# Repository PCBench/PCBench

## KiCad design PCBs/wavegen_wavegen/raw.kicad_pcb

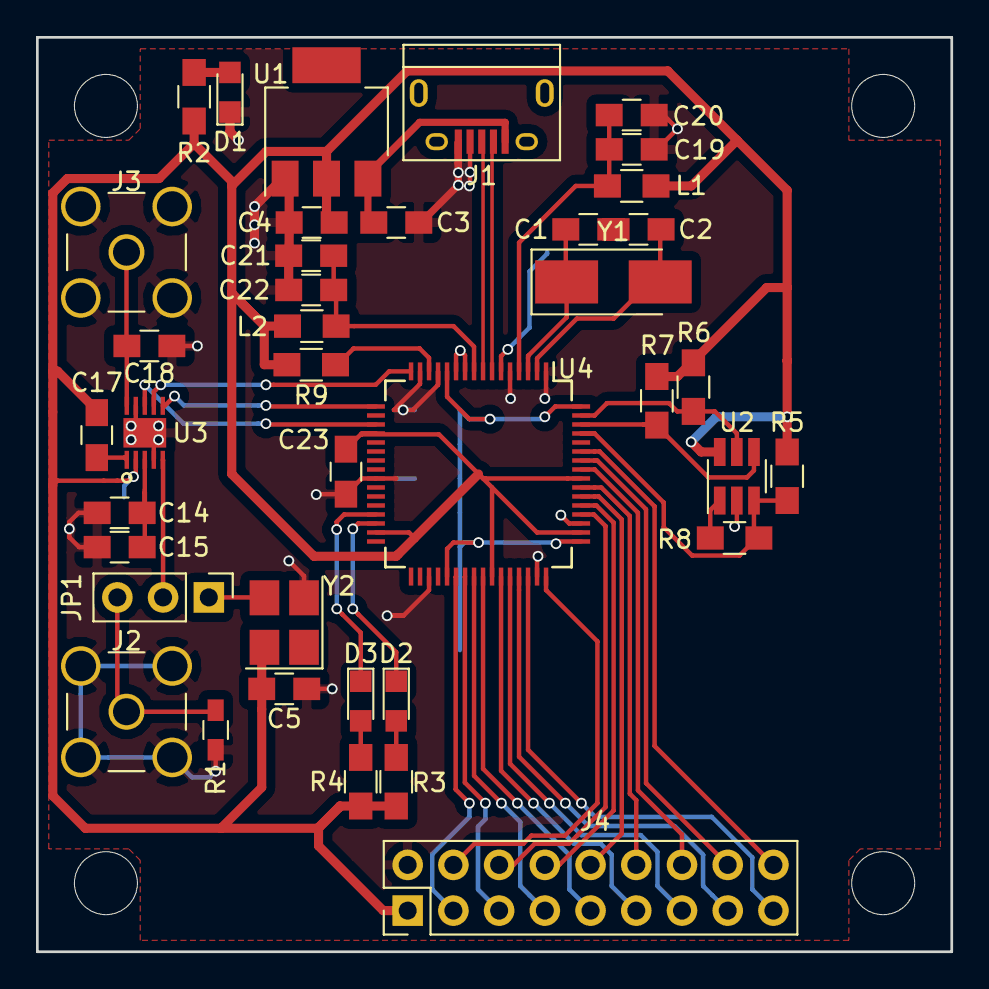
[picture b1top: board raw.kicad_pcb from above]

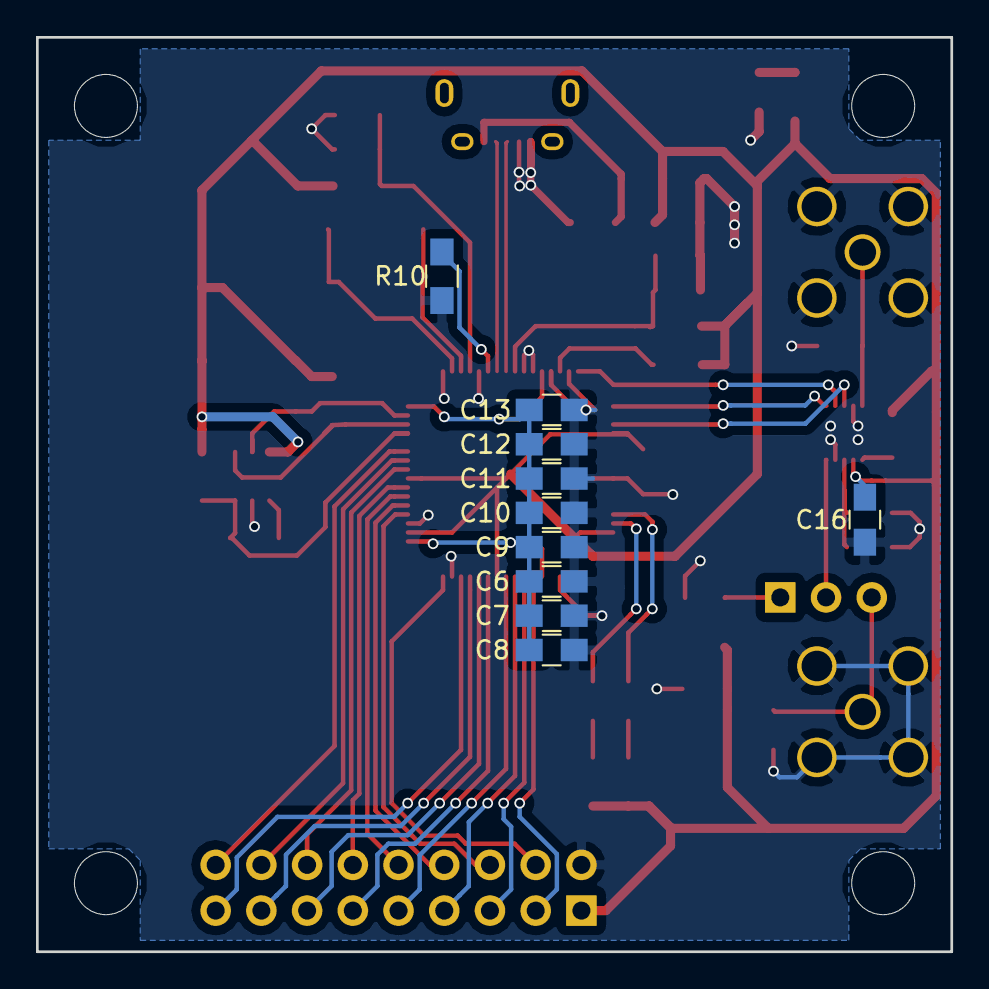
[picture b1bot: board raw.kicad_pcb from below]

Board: 2 copper layers, 50.8 x 50.8 mm, 49 parts (10 on the bottom side), 47 nets.

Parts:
C1, C2: 27p; C_0805_HandSoldering
C3, C5, C7, C8, C9, C10, C11, C12, C13, C14, C16, C18, C20, C22, C23: 100n; C_0805_HandSoldering
C4, C15: 10u; C_0805_HandSoldering
C6: 3.3u; C_0805_HandSoldering
C17: 10n; C_0805_HandSoldering
C19, C21: 4.7u; C_0805_HandSoldering
D1, D2, D3: LED_Small; LED_0805
J1: USB_B; USB_Micro-B
J2: EXT_CLK; SMA_THT_Jack_Straight
J3: VOUT; SMA_THT_Jack_Straight
J4: CONN_02X09; Pin_Header_Straight_2x09_Pitch2.54mm
JP1: CLK_SELECT; Pin_Header_Straight_1x03_Pitch2.54mm
L1, L2: 800m; L_0805_HandSoldering
R1: 50; R_0603_HandSoldering
R2, R3, R4: 470; R_0805_HandSoldering
R5, R6, R7: 10k; R_0805_HandSoldering
R8: 2.2k; R_0805_HandSoldering
R9: 1k; R_0805_HandSoldering
R10: 12k; R_0805_HandSoldering
U1: LD1117S33TR; SOT-223
U2: 93LC46BT; SOT-23-6_Handsoldering
U3: AD9837
U4: FT2232H; LQFP-64_10x10mm_Pitch0.5mm
Y1: 12MHz; Crystal_SMD_5032-2pin_5.0x3.2mm_HandSoldering
Y2: OXETGCJANF; Oscillator_SMD_Abracon_ASE-4pin_3.2x2.5mm_HandSoldering

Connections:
+3V3: C4.1, C5.1, C16.1, C17.1, C23.1, J4.1, L1.1, L2.1, R2.2, R3.2, R4.2, R5.1, R6.1, R7.1, R9.2, U1.2, U2.6, U3.2, U4.20, U4.31, U4.42, U4.50, U4.56, Y2.4
DAC_CLK: JP1.2, U3.5
EECLK: R7.2, U2.4, U4.62
EECS: R6.2, U2.5, U4.63
EEDATA: R5.2, R8.1, U2.3, U4.61
FTOSCI: C2.1, U4.2, Y1.2
FTOSCO: C1.1, U4.3, Y1.1
FTRXLED: D3.1, U4.29
FTTXLED: D2.1, U4.30
FTVPHY: C19.1, C20.1, L1.2, U4.4
FTVPLL: C21.1, C22.1, L2.2, U4.9
GNDA: C3.2, C4.2, C5.2, C6.2, C7.2, C8.2, C9.2, C10.2, C11.2, C12.2, C13.2, C14.2, C15.2, C16.2, C18.2, C19.2, C20.2, C21.2, C22.2, C23.2, D1.1, J1.4, J1.5, J2.2, J3.2, J4.2, R1.2, R10.2, U1.1, U2.2, U3.4, U3.9, U3.11, U4.1, U4.5, U4.10, U4.11, U4.13, U4.15, U4.25, U4.35, U4.47, U4.51, Y2.2
unnamed: C1.2, C2.2
unnamed: C3.1, J1.1, U1.3
unnamed: C6.1, C7.1, C8.1, C9.1, C10.1, C11.1, C12.1, C13.1, U4.12, U4.37, U4.49, U4.64
unnamed: C14.1, C15.1, U3.3
unnamed: C17.2, U3.1
unnamed: C18.1, J3.1, U3.10
unnamed: D1.2, R2.1
unnamed: D2.2, R3.1
unnamed: D3.2, R4.1
unnamed: J2.1, JP1.3, R1.1
unnamed: J4.3, U4.38
unnamed: J4.4, U4.48
unnamed: J4.5, U4.39
unnamed: J4.6, U4.52
unnamed: J4.7, U4.40
unnamed: J4.8, U4.53
unnamed: J4.9, U4.41
unnamed: J4.10, U4.54
unnamed: J4.11, U4.43
unnamed: J4.12, U4.55
unnamed: J4.13, U4.44
unnamed: J4.14, U4.57
unnamed: J4.15, U4.45
unnamed: J4.16, U4.58
unnamed: J4.17, U4.46
unnamed: J4.18, U4.59
unnamed: JP1.1, Y2.3
unnamed: R8.2, U2.1
unnamed: R9.1, U4.14
unnamed: R10.1, U4.6
unnamed: U3.6, U4.17
unnamed: U3.7, U4.16
unnamed: U3.8, U4.19
USB_D+: J1.3, U4.8
USB_D-: J1.2, U4.7

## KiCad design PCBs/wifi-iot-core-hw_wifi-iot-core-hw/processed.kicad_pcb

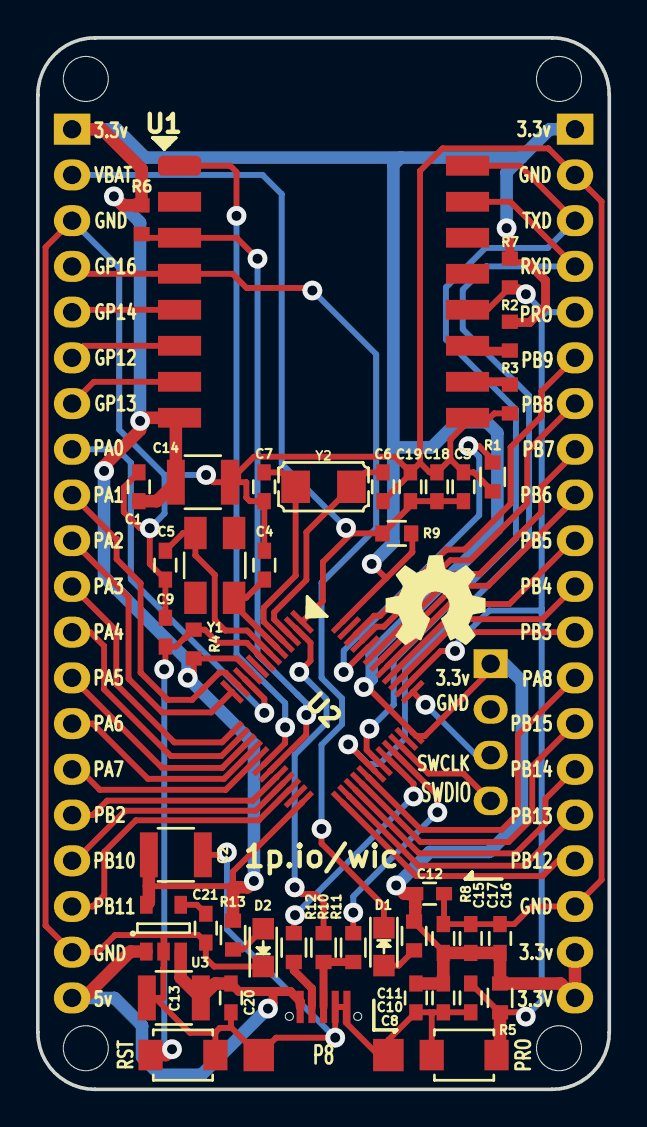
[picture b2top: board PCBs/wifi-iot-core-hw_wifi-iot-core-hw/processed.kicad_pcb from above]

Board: 2 copper layers, 31.8 x 58.4 mm, 52 parts (0 on the bottom side), 54 nets.

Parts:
C1, C9, C10, C11, C12, C15, C17, C19, C20: 0.1uF; C_0603
C2, C13, C14: 10uF-50v; C_1210
C3: 100nF; C_0603
C4, C5: 10pF; C_0603
C6: 15pF; C_0603
C7: 15pf; C_0603
C8: 470pF; C_0603
C16, C18: 1uF; C_0603
C21: 10nF; C_0603
D1: Led GPIO16; LED_0805
D2: Led; LED_0805
P1, P2: CONN_01X20; Pin_Header_Straight_1x20
P3, P4, P5, P6: CONN_01X01; MountingHole_2.5mm
P7: CONN_01X04; Pin_Header_Straight_1x04
P8: USB; Micro_usb_B_smd
PRO: SW_PUSH_SMALL_H; SW_SPST_B3U-1000P-B
R1, R6, R7, R8, R13: 10k; R_0603
R2, R3, R4, R5: 10K; R_0603
R9: 0R; R_0603
R10: 1.5K; R_0603
R11, R12: 22; R_0603
RST: RST; SW_SPST_B3U-1000P-B
U1: ESP-07v2; ESP-07v2-smd-16pin
U2: STM32F103C8Tx; LQFP-48_Pin1.7x0.3mm_Pitch0.5mm
U3: LP2985LV; SOT-23-5
VAL**: oshw_logo_500; logo5
Y1: 8MHz; Crystal_SMD_5032_4Pads
Y2: 32.687; crystal_smd_32.768_2Pin

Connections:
+3V3: C1.1, C2.1, C10.2, C11.2, C12.1, C14.1, C15.2, C16.2, C17.2, P1.1, P2.1, P2.19, P2.20, P7.1, R2.1, R4.2, R5.2, R6.1, R7.1, R8.1, R9.2, R13.1, U1.8, U2.9, U2.24, U2.36, U2.48, U3.5
+5V: C13.1, C20.1, P1.20, P8.1, U3.1, U3.3
/CH_PD: R6.2, U1.3, U2.19
/ESP_PRO: C8.1, P2.5, PRO.1, R5.1, R7.2, U1.12, U2.38
/ESP_RST: U1.1, U2.18
/ESP_RXD: P2.4, U1.15, U2.30
/ESP_TXD: P2.3, U1.16, U2.31
/GPIO16: D1.1, P1.4, U1.4
/RST: C9.1, R4.1, RST.1, U2.7
/SWCLK: P7.3, U2.37
/SWDIO: P7.4, U2.34
/USB_DIS: R10.1, U2.2
/USB_DM: R12.1, U2.32
/USB_DP: R11.1, U2.33
/VBAT: C3.2, C18.2, C19.2, P1.2, R9.1, U2.1
GNDREF: C1.2, C2.2, C3.1, C4.2, C5.2, C6.2, C7.2, C8.2, C9.2, C10.1, C11.1, C12.2, C13.2, C14.2, C15.1, C16.1, C17.1, C18.1, C19.1, C20.2, C21.2, D2.1, P1.3, P1.19, P2.2, P2.18, P8.4, P8.5, PRO.2, R1.2, R3.2, RST.2, U1.9, U3.2
GPIO12: P1.6, U1.6
GPIO13: P1.7, U1.7
GPIO14: P1.5, U1.5
unnamed: C4.1, U2.5, Y1.1
unnamed: C5.1, U2.6, Y1.2
unnamed: C6.1, U2.3, Y2.1
unnamed: C7.1, U2.4, Y2.2
unnamed: C21.1, U3.4
unnamed: D1.2, R8.2
unnamed: D2.2, R13.2
unnamed: P8.2, R12.2
unnamed: P8.3, R10.2, R11.2
unnamed: R1.1, U2.44
unnamed: R2.2, U1.11
unnamed: R3.1, U1.10
PA0: P1.8, U2.10
PA1: P1.9, U2.11
PA2: P1.10, U2.12
PA3: P1.11, U2.13
PA4: P1.12, U2.14
PA5: P1.13, U2.15
PA6: P1.14, U2.16
PA7: P1.15, U2.17
PA8: P2.13, U2.29
PB2: P1.16, U2.20
PB3: P2.12, U2.39
PB4: P2.11, U2.40
PB5: P2.10, U2.41
PB6: P2.9, U2.42
PB7: P2.8, U2.43
PB8: P2.7, U2.45
PB9: P2.6, U2.46
PB10: P1.17, U2.21
PB11: P1.18, U2.22
PB12: P2.17, U2.25
PB13: P2.16, U2.26
PB14: P2.15, U2.27
PB15: P2.14, U2.28

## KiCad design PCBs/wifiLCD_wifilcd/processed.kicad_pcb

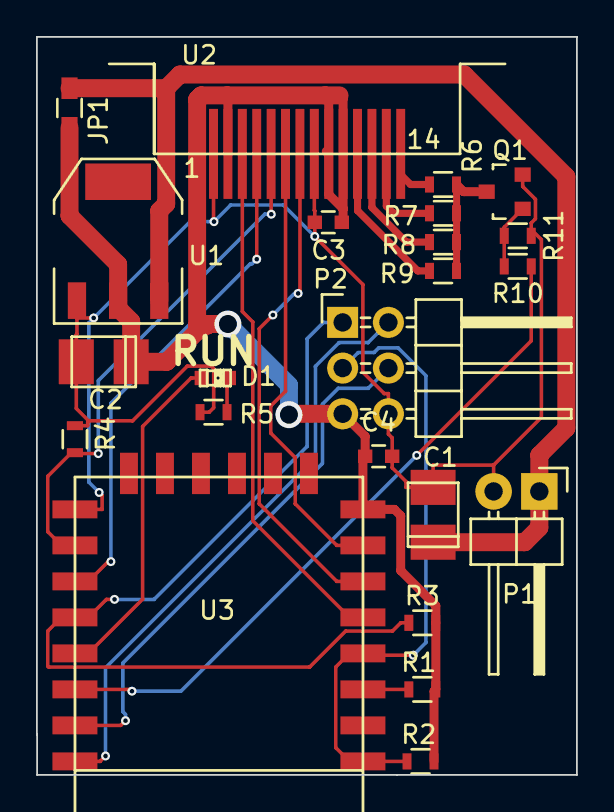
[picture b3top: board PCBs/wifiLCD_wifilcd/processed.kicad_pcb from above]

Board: 2 copper layers, 30.0 x 41.0 mm, 23 parts (0 on the bottom side), 22 nets.

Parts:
C1: 22uF 25V; TantalC_SizeT_EIA-3528
C2: 100uF 6.3v; TantalC_SizeT_EIA-3528
C3, C4: 100n; C_0603
D1: LED; LED-0603
JP1: JUMPER; R_0603_HandSoldering
P1: CONN_01X02; Pin_Header_Angled_1x02
P2: CONN_01X06; Pin_Header_Angled_2x03
Q1: BSS138; SOT-23
R1, R2, R3, R4: 10K; R_0603
R5: 220; R_0603
R6, R7, R8, R9: 4R7; R_0603
R10: 100k; R_0603
R11: 10; R_0603
U1: AP1117D33; SOT-223
U2: TM022HDH26; TM022HDH26_PADSONLY
U3: ESP-12E

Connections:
+3V3: C2.1, C3.1, C4.1, JP1.2, P2.5, R1.1, R2.1, R3.1, U1.2, U2.2, U2.9, U2.10, U3.8
+5V: C1.1, JP1.1, P1.1, U1.3
/BL: R11.2, U3.20
/CS: R4.1, U2.5, U3.16
/DC: U2.4, U3.17
/DTR: P2.1, R3.2, U3.18
/MISO: U2.7, U3.6
/MOSI: U2.6, U3.7
/RTS: P2.3, R2.2, U3.1, U3.4
/RX: P2.2, U3.22
/SCL: U2.3, U3.5
/TX: P2.4, U3.21
GND: C1.2, C2.2, C3.2, C4.2, P1.2, P2.6, Q1.2, R4.2, R5.2, R10.1, U1.1, U2.1, U2.8, U3.15
unnamed: D1.1, R5.1
unnamed: D1.2, U3.19
unnamed: Q1.1, R10.2, R11.1
unnamed: Q1.3, R6.1, R7.1, R8.1, R9.1
unnamed: R1.2, U3.3
unnamed: R6.2, U2.14
unnamed: R7.2, U2.13
unnamed: R8.2, U2.12
unnamed: R9.2, U2.11

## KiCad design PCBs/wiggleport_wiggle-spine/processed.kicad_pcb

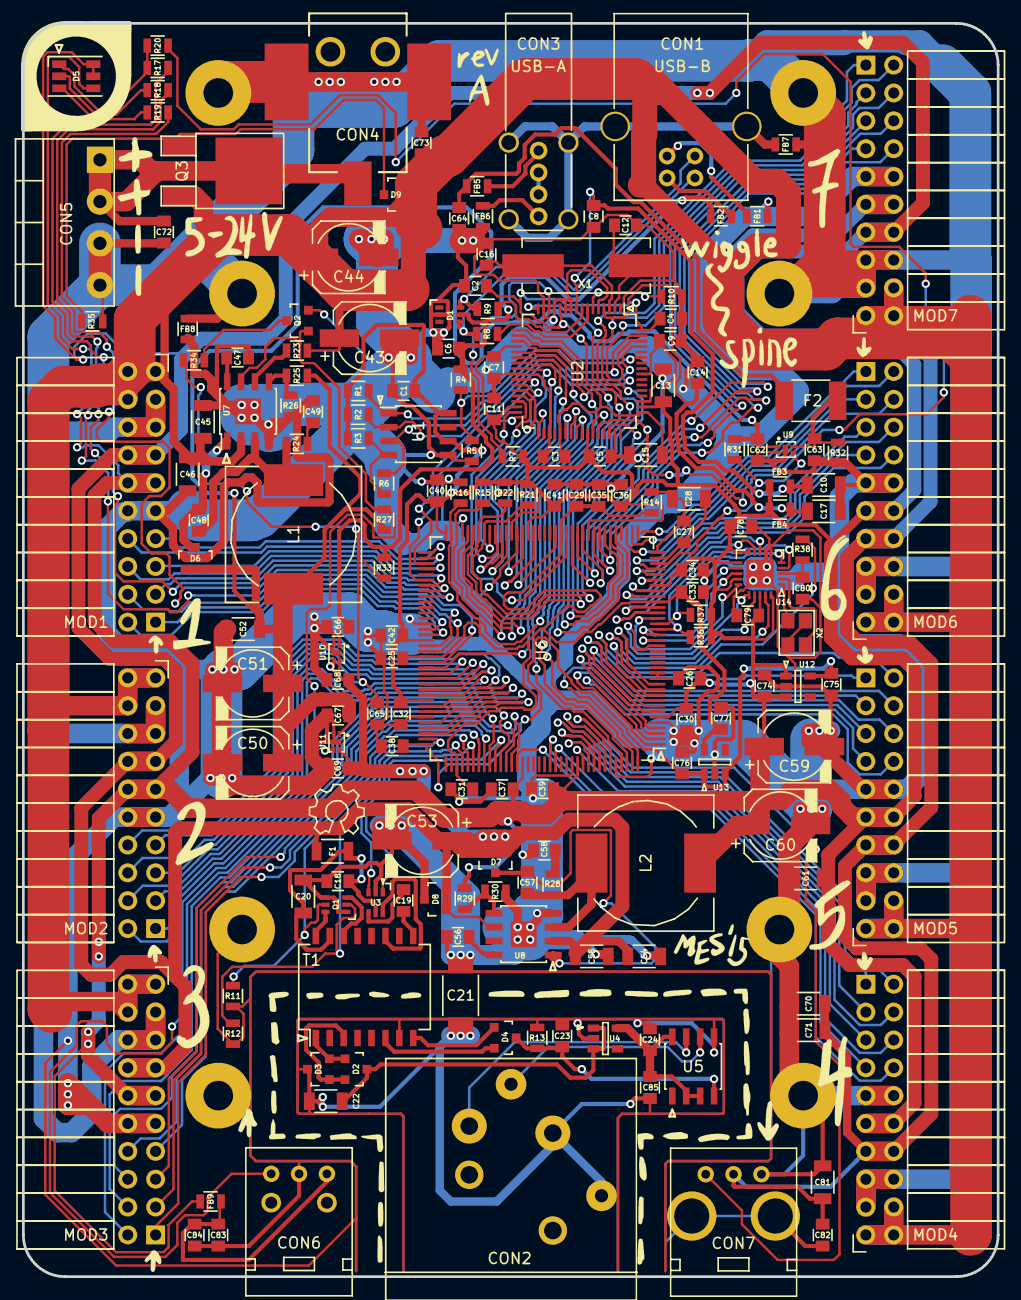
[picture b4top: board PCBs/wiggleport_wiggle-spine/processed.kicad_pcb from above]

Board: 2 copper layers, 88.9 x 114.3 mm, 179 parts (0 on the bottom side), 172 nets.

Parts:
C1, C2, C3, C4, C5, C6, C7, C8, C9, C11, C14, C18, C25, C26, C27, C29, C30, C31, C32, C33, C34, C35, C36, C37, C38, C39, C40, C41, C42, C48, C57, C63, C64, C65, C68, C69, C72, C74, C76, C78, C79, C82, C83, C85: 0.1uF; C_0805
C10, C13, C15, C17, C20, C22, C28, C45, C46, C52, C54, C55, C61, C70, C71, C81: 10uF; C_1206
C12, C16: 20pF; C_0805
C19, C23: 1nF; C_0805
C21: 1nF; C_1808
C24, C47, C56, C62, C66, C67, C73, C75, C77, C80, C84: 1uF; C_0805
C43, C44, C50, C51, C53, C59, C60: 22uF; c_elec_6.3x7.7
C49, C58: 100pF; C_0805
CON1: USB-B; USB_B
CON2: XLR-3 Female; XLR3MC
CON3: USB-A; USB_A_Vertical
CON4: 2.5mm 5-24V 5A; BARREL_JACK
CON5: 5-24V 16A; TerminalBlock_Pheonix_PT-3.5mm_4pol
CON6: PLR135; Everlight-PLR135-T8
CON7: PLT133; Everlight-PLT133-T6A
D1: TVS DIODE 5.5VWM; SC-70-6
D2, D4, D6, D7: BAT54 2x common cathode; SOT-23
D3: BAT54 2x common anode; SOT-23
D5: LED_BGR; LED_RGB_PLLC-6
D8, D9: 8.5VWM; SOT-23
F1: 200mA PTC; R_1206
F2: 2A PTC; R_1812
FB1, FB2, FB3, FB4, FB5, FB6, FB7, FB8, FB9: Ferrite bead; R_0805
L1, L2: 22uH; COIL_SMD_6mm_1mmCrtYd
MOD1, MOD2, MOD3, MOD4, MOD5, MOD6, MOD7: 2.54mm 2x10 right angle female header; Socket_Strip_Angled_2x10_Mirror
Q1: DMN3190LDW; SC-70-6
Q2: 2N7002P; SOT-23
Q3: AOD4189; TO-252-2Lead
R1, R2, R3, R5, R11, R12, R15, R16, R21, R22, R38: 10k; R_0805
R4, R7: 4.7k; R_0805
R6, R34, R36, R37: 2.2k; R_0805
R8, R9: 10; R_0805
R10: 12k 1%; R_0805
R13, R19: 240; R_0805
R14, R24, R28: 150; R_0805
R17, R18: 750; R_0805
R20, R29: 16k 1%; R_0805
R23, R27, R31, R32, R33, R35: 100k; R_0805
R25: 27k 1%; R_0805
R26, R30: 5.1k 1%; R_0805
T1: 10/100baseT transformer; SOIC-16_7.5x10.3mm_Pitch1.27mm
U1: 93C56; SOIC-8_3.9x4.9mm_Pitch1.27mm
U2: FT2232H; LQFP-64_10x10mm_Pitch0.5mm
U3: NC7WZ14; SC-70-6
U4: AP2204K-5.0; SOT-23-5
U5: ST485E; SOIC-8_3.9x4.9mm_Pitch1.27mm
U6: iCE40-HX1K-TQ144; TQFP-144_20x20mm_Pitch0.5mm
U7, U8: RT8299A; SOIC-8-1EP_3.9x4.9mm_Pitch1.27mm
U9, U10, U11: SiP32408; TDFN4
U12: TCR2EF25; SOT-23-5
U13: TCR2EF12; SOT-23-5
U14: Si5351B; QFN-20-1EP_4x4mm_Pitch0.5mm
X1: 12 MHz; Crystal_HC49-SD_SMD
X2: 25.0000 MHz 15ppm 8pF; crystal_FA238-TSX3225

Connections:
+1V2: C25.2, C29.2, C31.2, C33.2, C35.2, C77.1, R14.2, U6.27, U6.51, U6.92, U6.111, U13.5
+2V5: C38.2, C75.1, C76.2, U6.108, U12.5, U13.1, U13.3
+3V3: C1.2, C5.2, C7.2, C9.2, C11.2, C13.1, C26.2, C30.2, C32.2, C34.2, C36.2, C37.2, C39.2, C40.2, C41.2, C42.2, C59.1, C60.1, C61.1, C74.2, C78.2, C79.2, D5.4, FB3.1, FB4.1, FB9.1, L2.2, MOD1.11, MOD1.12, MOD2.11, MOD2.12, MOD3.11, MOD3.12, MOD4.11, MOD4.12, MOD5.11, MOD5.12, MOD6.11, MOD6.12, MOD7.11, MOD7.12, R1.2, R2.2, R3.2, R7.2, R15.2, R21.2, R22.2, R29.2, R36.1, R37.1, U1.6, U1.8, U2.20, U2.31, U2.42, U2.50, U2.56, U6.6, U6.30, U6.46, U6.57, U6.72, U6.89, U6.100, U6.123, U6.133, U12.1, U12.3, U14.10, U14.11, U14.14, U14.18, U14.20
+5V: C53.1, C54.1, C55.1, C68.2, C69.2, C70.1, C71.1, C81.1, C82.2, CON7.2, D5.5, D5.6, D7.1, D7.2, D8.1, D8.2, F1.2, MOD1.13, MOD1.14, MOD2.13, MOD2.14, MOD3.13, MOD3.14, MOD4.13, MOD4.14, MOD5.13, MOD5.14, MOD6.13, MOD6.14, MOD7.13, MOD7.14, U8.2, U8.6, U10.4, U11.4
+24V: C43.1, C44.1, C45.1, C46.1, C73.1, D9.1, D9.2, MOD1.18, MOD1.19, MOD1.20, MOD2.18, MOD2.19, MOD2.20, MOD3.18, MOD3.19, MOD3.20, MOD4.18, MOD4.19, MOD4.20, MOD5.18, MOD5.19, MOD5.20, MOD6.18, MOD6.19, MOD6.20, MOD7.18, MOD7.19, MOD7.20, Q3.3, R23.1, U7.2
/Clock Source/CLK0: U6.20, U14.13
/Clock Source/CLK1: U6.21, U14.12
/Clock Source/CLK2: U6.25, U14.9
/Clock Source/CLK3: U6.26, U14.8
/Clock Source/CLK4: U6.11, U14.19
/Clock Source/CLK5: U6.12, U14.17
/Clock Source/CLK6: U6.19, U14.16
/Clock Source/CLK7: U6.24, U14.15
/Clock Source/VCXO_PWM: R38.1, U6.10
/DMX512/DMXGND: C21.1, C22.2, C23.2, C24.2, C85.1, CON2.1, CON2.G, D3.3, R13.1, T1.7, U4.2, U5.5
/FPGA/BLUE_N: R17.1, U6.81
/FPGA/CDONE: R20.2, R21.1, U2.44, U6.65
/FPGA/CLK_SCL: R36.2, U6.22, U14.4
/FPGA/CLK_SDA: R37.2, U6.23, U14.5
/FPGA/CRESET_B: R22.1, U2.46, U6.66
/FPGA/DMX_GATE1: Q1.2, R12.1, U6.112
/FPGA/DMX_GATE2: Q1.5, R11.1, U6.107
/FPGA/DMX_TX1: U3.1, U6.118
/FPGA/DMX_TX2: U3.3, U6.114
/FPGA/FIFO_CLKOUT: U2.32, U6.50
/FPGA/FIFO_DATA0: U2.16, U6.142
/FPGA/FIFO_DATA1: U2.17, U6.141
/FPGA/FIFO_DATA2: U2.18, U6.42
/FPGA/FIFO_DATA3: U2.19, U6.94
/FPGA/FIFO_DATA4: U2.21, U6.52
/FPGA/FIFO_DATA5: U2.22, U6.56
/FPGA/FIFO_DATA6: U2.23, U6.58
/FPGA/FIFO_DATA7: U2.24, U6.61
/FPGA/FIFO_OE#: U2.33, U6.60
/FPGA/FIFO_RD#: U2.28, U6.64
/FPGA/FIFO_RXF#: U2.26, U6.75
/FPGA/FIFO_SIWU: U2.30, U6.78
/FPGA/FIFO_TXE#: U2.27, U6.62
/FPGA/FIFO_WR#: U2.29, U6.63
/FPGA/GREEN_N: R18.1, U6.90
/FPGA/RED_N: R19.1, U6.93
/FPGA/SYNC_TXD: CON7.3, U6.139
/FPGA/VBUS_DOWNSTREAM_EN: R31.1, U6.34, U9.3
/Power/5-24V Power Input/POWER_IN: C72.2, CON4.1, CON5.1, CON5.2, Q3.2
/Power/5-24V to 5V Converter/CONVERTED_5V_OKAY: Q2.1, R27.1, U7.7, U11.3
/Power/USB Power Output/5V_IN: C50.1, C51.1, C52.1, C62.1, C67.1, D6.1, D6.2, L1.2, R25.2, R27.2, R31.2, U9.1, U11.1
/Power/VBUS_UPSTREAM: C6.2, C66.1, D1.5, FB2.2, R4.2, R33.1, U10.1
/Sync In/Out/RXD: CON6.3, U6.105
/USB/EECLK: R2.1, U1.2, U2.62
/USB/EECS: R1.1, U1.1, U2.63
/USB/EEDATA: R6.2, U1.3, U2.61
/USB/EEDATA_OUT: R3.1, R6.1, U1.4
/USB/FTDI_1V8REG: C2.2, C3.2, C4.2, C15.1, U2.12, U2.37, U2.49, U2.64
/USB/FTDI_VPHY: C14.2, C17.1, FB4.2, U2.4
/USB/FTDI_VPLL: C8.2, C10.1, FB3.2, U2.9
/USB/GPIO_L0: R16.2, U2.43, U6.71
/USB/SPI_CLK: R15.1, U2.38, U6.70
/USB/SPI_DI: U2.40, U6.67
/USB/SPI_DO: U2.39, U6.68
/USB/VBUS_SENSE: R4.1, R5.2, U2.59
Earth: CON1.5, CON3.5, FB7.2
GND: C1.1, C2.1, C3.1, C4.1, C5.1, C6.1, C7.1, C8.1, C9.1, C10.2, C11.1, C12.1, C13.2, C14.1, C15.2, C16.1, C17.2, C18.1, C20.2, C21.2, C25.1, C26.1, C29.1, C30.1, C31.1, C32.1, C33.1, C34.1, C35.1, C36.1, C37.1, C38.1, C39.1, C40.1, C41.1, C42.1, C43.2, C44.2, C45.2, C46.2, C47.2, C49.1, C50.2, C51.2, C52.2, C53.2, C54.2, C55.2, C56.2, C58.1, C59.2, C60.2, C61.2, C62.2, C63.1, C64.1, C65.1, C66.2, C67.2, C68.1, C69.1, C70.2, C71.2, C74.1, C75.2, C76.1, C77.2, C78.1, C79.1, C80.2, C81.2, C82.1, C83.1, C84.2, CON6.2, CON7.1, D1.2, D8.3, FB1.1, FB6.1, FB8.2, MOD1.9, MOD1.10, MOD2.9, MOD2.10, MOD3.9, MOD3.10, MOD4.9, MOD4.10, MOD5.9, MOD5.10, MOD6.9, MOD6.10, MOD7.9, MOD7.10, Q1.1, Q1.4, Q2.2, R5.1, R10.1, R11.2, R12.2, R16.1, R26.1, R30.1, R32.2, U1.5, U2.1, U2.5, U2.10, U2.11, U2.13, U2.15, U2.25, U2.35, U2.47, U2.51, U3.2, U6.5, U6.13, U6.14, U6.59, U6.69, U6.86, U6.103, U6.132, U6.140, U7.4, U7.9, U8.4, U8.9, U9.2, U9.5, U10.2, U10.5, U11.2, U11.5, U12.2, U13.2, U14.6, U14.7, U14.21, X2.2, X2.4
GNDPWR: C72.1, C73.2, CON4.2, CON4.3, CON5.3, CON5.4, FB7.1, FB8.1, MOD1.15, MOD1.16, MOD1.17, MOD2.15, MOD2.16, MOD2.17, MOD3.15, MOD3.16, MOD3.17, MOD4.15, MOD4.16, MOD4.17, MOD5.15, MOD5.16, MOD5.17, MOD6.15, MOD6.16, MOD6.17, MOD7.15, MOD7.16, MOD7.17, R35.2
MOD1_PIN1: MOD1.1, U6.87
MOD1_PIN2: MOD1.2, U6.88
MOD1_PIN3: MOD1.3, U6.80
MOD1_PIN4: MOD1.4, U6.91
MOD1_PIN5: MOD1.5, U6.76
MOD1_PIN6: MOD1.6, U6.79
MOD1_PIN7: MOD1.7, U6.73
MOD1_PIN8: MOD1.8, U6.74
MOD2_PIN1: MOD2.1, U6.102
MOD2_PIN2: MOD2.2, U6.104
MOD2_PIN3: MOD2.3, U6.99
MOD2_PIN4: MOD2.4, U6.98
MOD2_PIN5: MOD2.5, U6.97
MOD2_PIN6: MOD2.6, U6.96
MOD2_PIN7: MOD2.7, U6.95
MOD2_PIN8: MOD2.8, U6.101
MOD3_PIN1: MOD3.1, U6.113
MOD3_PIN2: MOD3.2, U6.106
MOD3_PIN3: MOD3.3, U6.115
MOD3_PIN4: MOD3.4, U6.119
MOD3_PIN5: MOD3.5, U6.116
MOD3_PIN6: MOD3.6, U6.117
MOD3_PIN7: MOD3.7, U6.121
MOD3_PIN8: MOD3.8, U6.120
MOD4_PIN1: MOD4.1, U6.137
MOD4_PIN2: MOD4.2, U6.138
MOD4_PIN3: MOD4.3, U6.136
MOD4_PIN4: MOD4.4, U6.135
MOD4_PIN5: MOD4.5, U6.134
MOD4_PIN6: MOD4.6, U6.129
MOD4_PIN7: MOD4.7, U6.128
MOD4_PIN8: MOD4.8, U6.122
MOD5_PIN1: MOD5.1, U6.8
MOD5_PIN2: MOD5.2, U6.9
MOD5_PIN3: MOD5.3, U6.4
MOD5_PIN4: MOD5.4, U6.7
MOD5_PIN5: MOD5.5, U6.144
MOD5_PIN6: MOD5.6, U6.3
MOD5_PIN7: MOD5.7, U6.1
MOD5_PIN8: MOD5.8, U6.2
MOD6_PIN1: MOD6.1, U6.37
MOD6_PIN2: MOD6.2, U6.38
MOD6_PIN3: MOD6.3, U6.39
MOD6_PIN4: MOD6.4, U6.33
MOD6_PIN5: MOD6.5, U6.32
MOD6_PIN6: MOD6.6, U6.31
MOD6_PIN7: MOD6.7, U6.29
MOD6_PIN8: MOD6.8, U6.28
MOD7_PIN1: MOD7.1, U6.143
MOD7_PIN2: MOD7.2, U6.41
MOD7_PIN3: MOD7.3, U6.43
MOD7_PIN4: MOD7.4, U6.45
MOD7_PIN5: MOD7.5, U6.44
MOD7_PIN6: MOD7.6, U6.47
MOD7_PIN7: MOD7.7, U6.48
MOD7_PIN8: MOD7.8, U6.49
unnamed: C12.2, U2.2, X1.1
unnamed: C16.2, U2.3, X1.2
unnamed: C18.2, C20.1, F1.1, T1.15, U3.5
unnamed: C19.1, T1.9
unnamed: C19.2, U3.4
unnamed: C22.1, D2.3, U4.1, U4.3
unnamed: C23.1, D4.3, R13.2, U5.4
unnamed: C24.1, C85.2, U4.5, U5.2, U5.3, U5.8
unnamed: C27.1, C28.2, U6.35
unnamed: C27.2, C28.1, R14.1, U6.36
unnamed: C47.1, U7.8
unnamed: C48.1, L1.1, R24.2, U7.3
unnamed: C48.2, D6.3, U7.1
unnamed: C49.2, R24.1
unnamed: C56.1, U8.8
unnamed: C57.1, L2.1, R28.2, U8.3
unnamed: C57.2, D7.3, U8.1
unnamed: C58.2, R28.1
unnamed: C63.2, F2.1, R32.1, U9.4
unnamed: C64.2, F2.2, FB5.1
unnamed: C65.2, R33.2, R34.1, U10.3
unnamed: C80.1, R38.2, U14.3
unnamed: C83.2, C84.1, CON6.1, FB9.2
unnamed: CON1.1, FB2.1
unnamed: CON1.2, D1.4, R8.1
unnamed: CON1.3, D1.6, R9.1
unnamed: CON1.4, FB1.2
unnamed: CON2.2, U5.7
unnamed: CON2.3, U5.6
unnamed: CON3.1, FB5.2
unnamed: CON3.2, CON3.3
unnamed: CON3.4, FB6.2
unnamed: D2.1, D3.2, T1.1
unnamed: D2.2, D3.1, T1.3
unnamed: D4.1, T1.8
unnamed: D4.2, T1.6
unnamed: D5.1, R17.2, R20.1
unnamed: D5.2, R18.2
unnamed: D5.3, R19.2
unnamed: D9.3, Q3.1, R35.1
unnamed: Q1.3, T1.14
unnamed: Q1.6, T1.16
unnamed: Q2.3, R34.2
unnamed: R7.1, U2.14
unnamed: R8.2, U2.7
unnamed: R9.2, U2.8
unnamed: R10.2, U2.6
unnamed: R23.2, U7.6
unnamed: R25.1, R26.2, U7.5
unnamed: R29.1, R30.2, U8.5
unnamed: T1.11, U3.6
unnamed: U14.1, X2.1
unnamed: U14.2, X2.3

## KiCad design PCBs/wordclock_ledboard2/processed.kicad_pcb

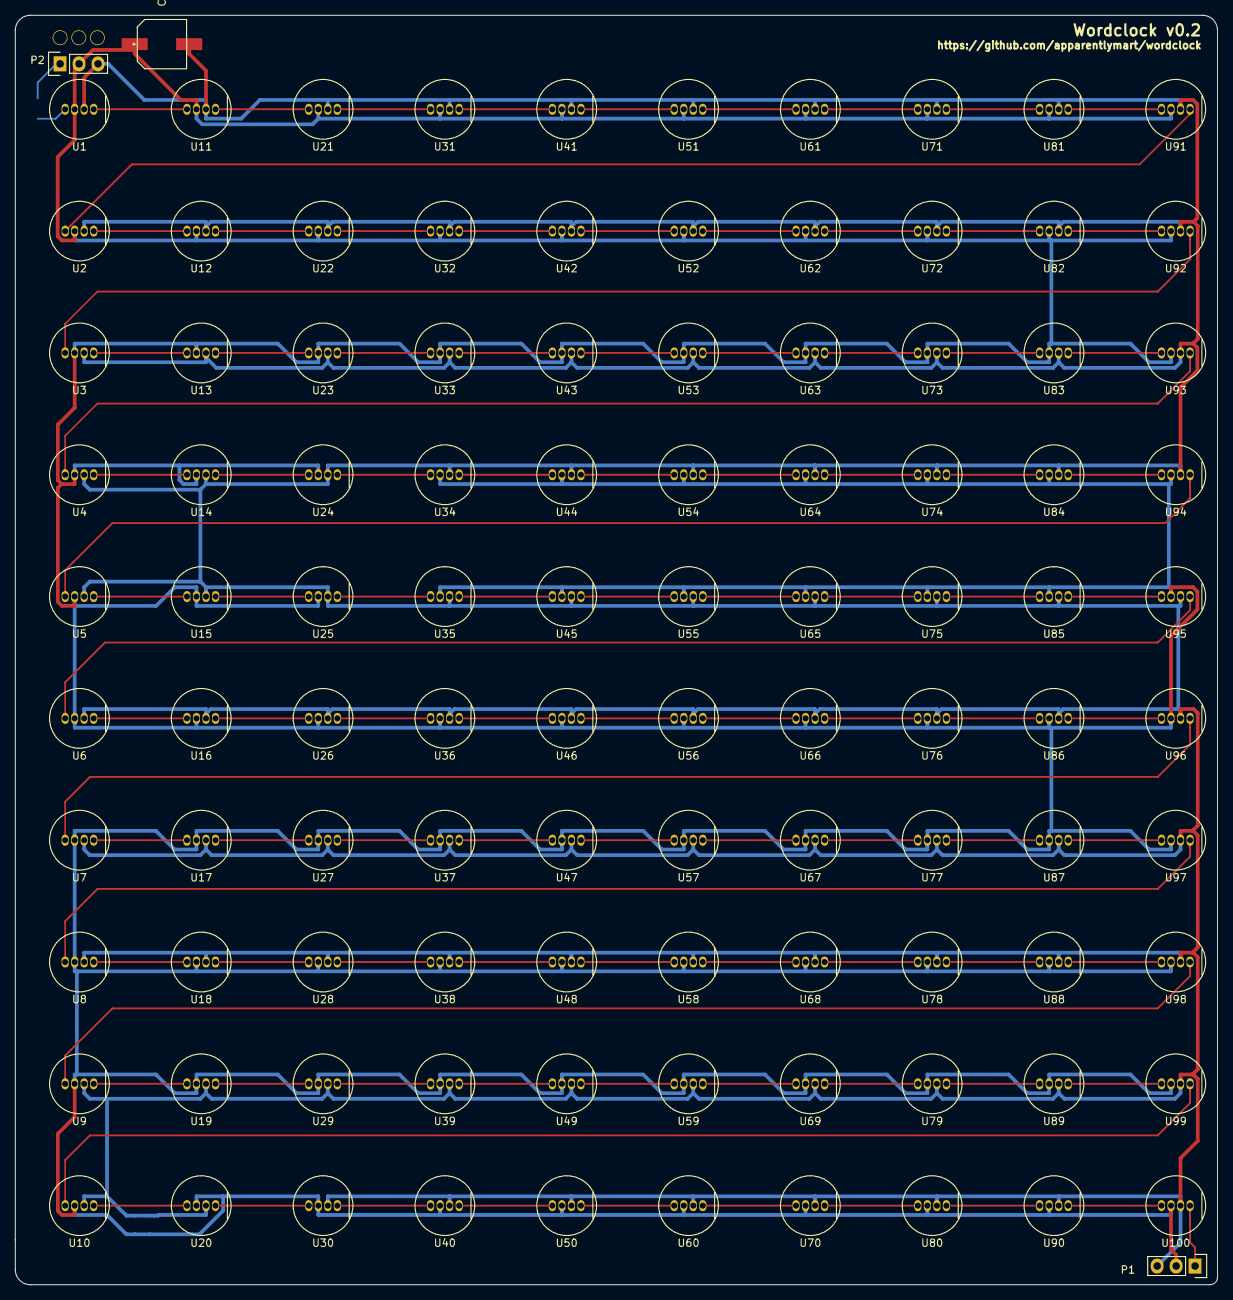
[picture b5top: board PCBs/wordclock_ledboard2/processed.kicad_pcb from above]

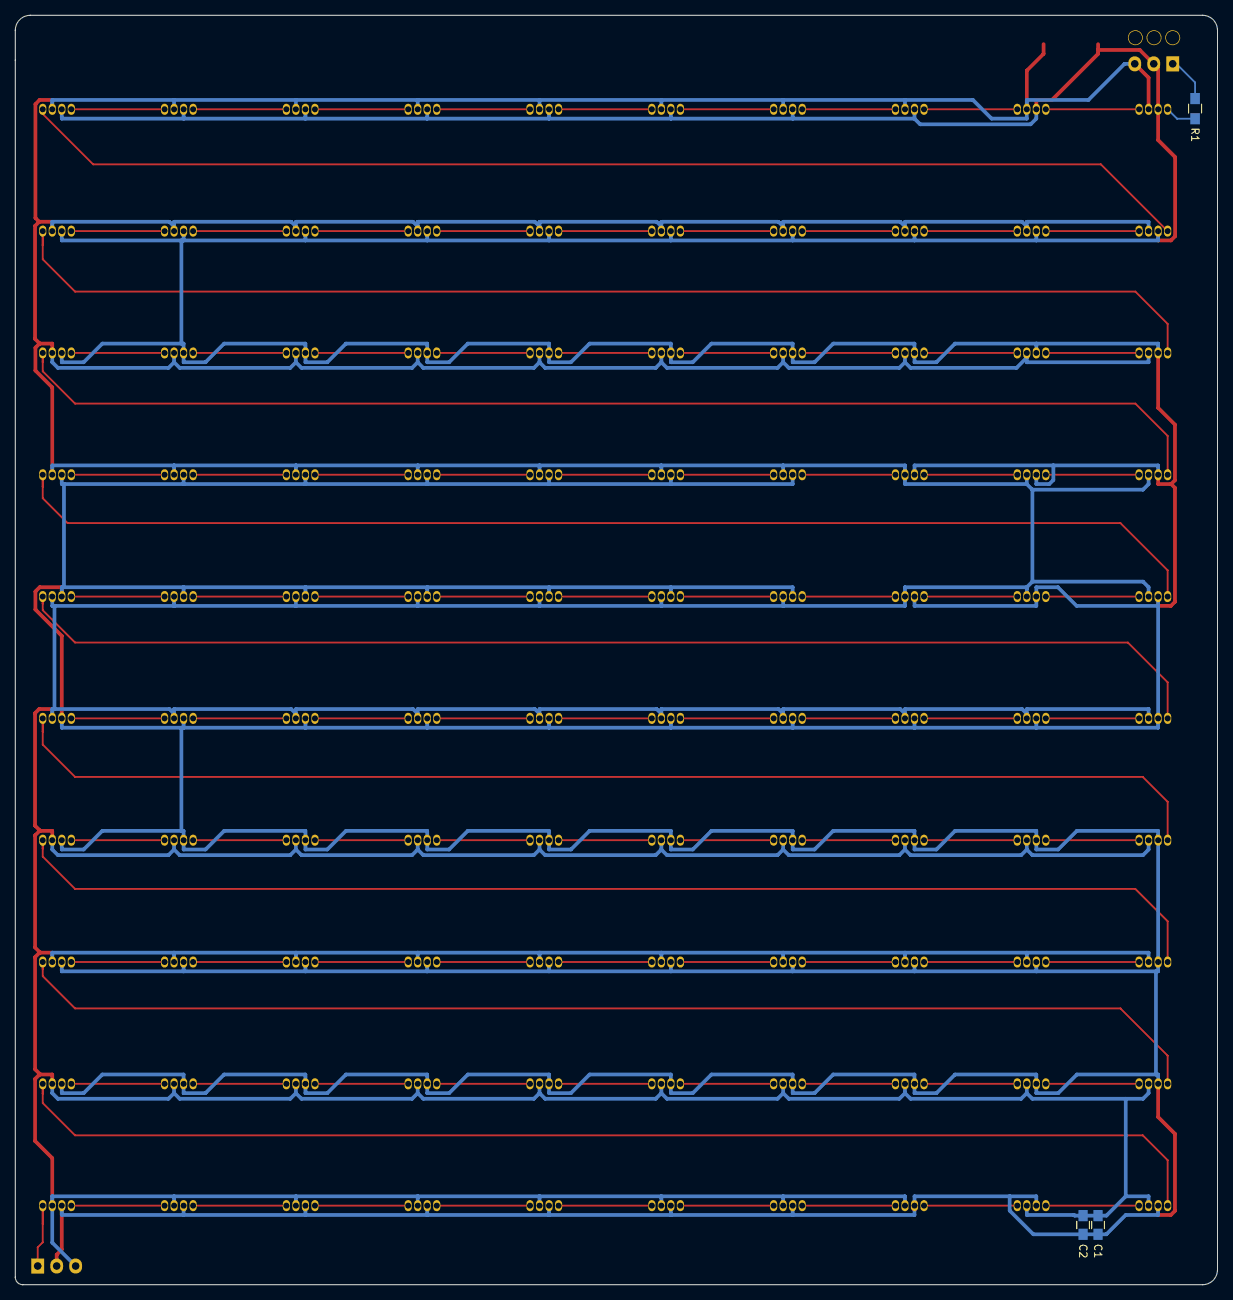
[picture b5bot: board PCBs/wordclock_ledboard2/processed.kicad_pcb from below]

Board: 2 copper layers, 161.0 x 170.0 mm, 106 parts (3 on the bottom side), 104 nets.

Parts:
C1, C2: 0.1u; C_0805_HandSoldering
C3: CP; CPOL_SMD_6.3mm
P1, P2: CONN_01X03; Pin_Header_Straight_1x03
R1: 300; R_0805_HandSoldering
U1, U2, U3, U4, U5, U6, U7, U8, U9, U10, U11, U12, U13, U14, U15, U16, U17, U18, U19, U20, U21, U22, U23, U24, U25, U26, U27, U28, U29, U30, U31, U32, U33, U34, U35, U36, U37, U38, U39, U40, U41, U42, U43, U44, U45, U46, U47, U48, U49, U50, U51, U52, U53, U54, U55, U56, U57, U58, U59, U60, U61, U62, U63, U64, U65, U66, U67, U68, U69, U70, U71, U72, U73, U74, U75, U76, U77, U78, U79, U80, U81, U82, U83, U84, U85, U86, U87, U88, U89, U90, U91, U92, U93, U94, U95, U96, U97, U98, U99, U100: NEOPIXEL; NEOPIXEL_8MM

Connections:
+5V: C1.1, C2.1, C3.1, P1.2, P2.2, U1.2, U2.2, U3.2, U4.2, U5.2, U6.2, U7.2, U8.2, U9.2, U10.2, U11.2, U12.2, U13.2, U14.2, U15.2, U16.2, U17.2, U18.2, U19.2, U20.2, U21.2, U22.2, U23.2, U24.2, U25.2, U26.2, U27.2, U28.2, U29.2, U30.2, U31.2, U32.2, U33.2, U34.2, U35.2, U36.2, U37.2, U38.2, U39.2, U40.2, U41.2, U42.2, U43.2, U44.2, U45.2, U46.2, U47.2, U48.2, U49.2, U50.2, U51.2, U52.2, U53.2, U54.2, U55.2, U56.2, U57.2, U58.2, U59.2, U60.2, U61.2, U62.2, U63.2, U64.2, U65.2, U66.2, U67.2, U68.2, U69.2, U70.2, U71.2, U72.2, U73.2, U74.2, U75.2, U76.2, U77.2, U78.2, U79.2, U80.2, U81.2, U82.2, U83.2, U84.2, U85.2, U86.2, U87.2, U88.2, U89.2, U90.2, U91.2, U92.2, U93.2, U94.2, U95.2, U96.2, U97.2, U98.2, U99.2, U100.2
DIN: P2.1, R1.2
DOUT: P1.1, U100.4
GND: C1.2, C2.2, C3.2, P1.3, P2.3, U1.3, U2.3, U3.3, U4.3, U5.3, U6.3, U7.3, U8.3, U9.3, U10.3, U11.3, U12.3, U13.3, U14.3, U15.3, U16.3, U17.3, U18.3, U19.3, U20.3, U21.3, U22.3, U23.3, U24.3, U25.3, U26.3, U27.3, U28.3, U29.3, U30.3, U31.3, U32.3, U33.3, U34.3, U35.3, U36.3, U37.3, U38.3, U39.3, U40.3, U41.3, U42.3, U43.3, U44.3, U45.3, U46.3, U47.3, U48.3, U49.3, U50.3, U51.3, U52.3, U53.3, U54.3, U55.3, U56.3, U57.3, U58.3, U59.3, U60.3, U61.3, U62.3, U63.3, U64.3, U65.3, U66.3, U67.3, U68.3, U69.3, U70.3, U71.3, U72.3, U73.3, U74.3, U75.3, U76.3, U77.3, U78.3, U79.3, U80.3, U81.3, U82.3, U83.3, U84.3, U85.3, U86.3, U87.3, U88.3, U89.3, U90.3, U91.3, U92.3, U93.3, U94.3, U95.3, U96.3, U97.3, U98.3, U99.3, U100.3
unnamed: R1.1, U1.1
unnamed: U1.4, U11.1
unnamed: U2.1, U91.4
unnamed: U3.1, U92.4
unnamed: U4.1, U93.4
unnamed: U5.1, U94.4
unnamed: U6.1, U95.4
unnamed: U7.1, U96.4
unnamed: U8.1, U97.4
unnamed: U9.1, U98.4
unnamed: U10.1, U99.4
unnamed: U10.4, U20.1
unnamed: U11.4, U21.1
unnamed: U2.4, U12.1
unnamed: U12.4, U22.1
unnamed: U3.4, U13.1
unnamed: U13.4, U23.1
unnamed: U4.4, U14.1
unnamed: U14.4, U24.1
unnamed: U5.4, U15.1
unnamed: U15.4, U25.1
unnamed: U6.4, U16.1
unnamed: U16.4, U26.1
unnamed: U7.4, U17.1
unnamed: U17.4, U27.1
unnamed: U8.4, U18.1
unnamed: U18.4, U28.1
unnamed: U9.4, U19.1
unnamed: U19.4, U29.1
unnamed: U20.4, U30.1
unnamed: U21.4, U31.1
unnamed: U22.4, U32.1
unnamed: U23.4, U33.1
unnamed: U24.4, U34.1
unnamed: U25.4, U35.1
unnamed: U26.4, U36.1
unnamed: U27.4, U37.1
unnamed: U28.4, U38.1
unnamed: U29.4, U39.1
unnamed: U30.4, U40.1
unnamed: U31.4, U41.1
unnamed: U32.4, U42.1
unnamed: U33.4, U43.1
unnamed: U34.4, U44.1
unnamed: U35.4, U45.1
unnamed: U36.4, U46.1
unnamed: U37.4, U47.1
unnamed: U38.4, U48.1
unnamed: U39.4, U49.1
unnamed: U40.4, U50.1
unnamed: U41.4, U51.1
unnamed: U42.4, U52.1
unnamed: U43.4, U53.1
unnamed: U44.4, U54.1
unnamed: U45.4, U55.1
unnamed: U46.4, U56.1
unnamed: U47.4, U57.1
unnamed: U48.4, U58.1
unnamed: U49.4, U59.1
unnamed: U50.4, U60.1
unnamed: U51.4, U61.1
unnamed: U52.4, U62.1
unnamed: U53.4, U63.1
unnamed: U54.4, U64.1
unnamed: U55.4, U65.1
unnamed: U56.4, U66.1
unnamed: U57.4, U67.1
unnamed: U58.4, U68.1
unnamed: U59.4, U69.1
unnamed: U60.4, U70.1
unnamed: U61.4, U71.1
unnamed: U62.4, U72.1
unnamed: U63.4, U73.1
unnamed: U64.4, U74.1
unnamed: U65.4, U75.1
unnamed: U66.4, U76.1
unnamed: U67.4, U77.1
unnamed: U68.4, U78.1
unnamed: U69.4, U79.1
unnamed: U70.4, U80.1
unnamed: U71.4, U81.1
unnamed: U72.4, U82.1
unnamed: U73.4, U83.1
unnamed: U74.4, U84.1
unnamed: U75.4, U85.1
unnamed: U76.4, U86.1
unnamed: U77.4, U87.1
unnamed: U78.4, U88.1
unnamed: U79.4, U89.1
unnamed: U80.4, U90.1
unnamed: U81.4, U91.1
unnamed: U82.4, U92.1
unnamed: U83.4, U93.1
unnamed: U84.4, U94.1
unnamed: U85.4, U95.1
unnamed: U86.4, U96.1
unnamed: U87.4, U97.1
unnamed: U88.4, U98.1
unnamed: U89.4, U99.1
unnamed: U90.4, U100.1

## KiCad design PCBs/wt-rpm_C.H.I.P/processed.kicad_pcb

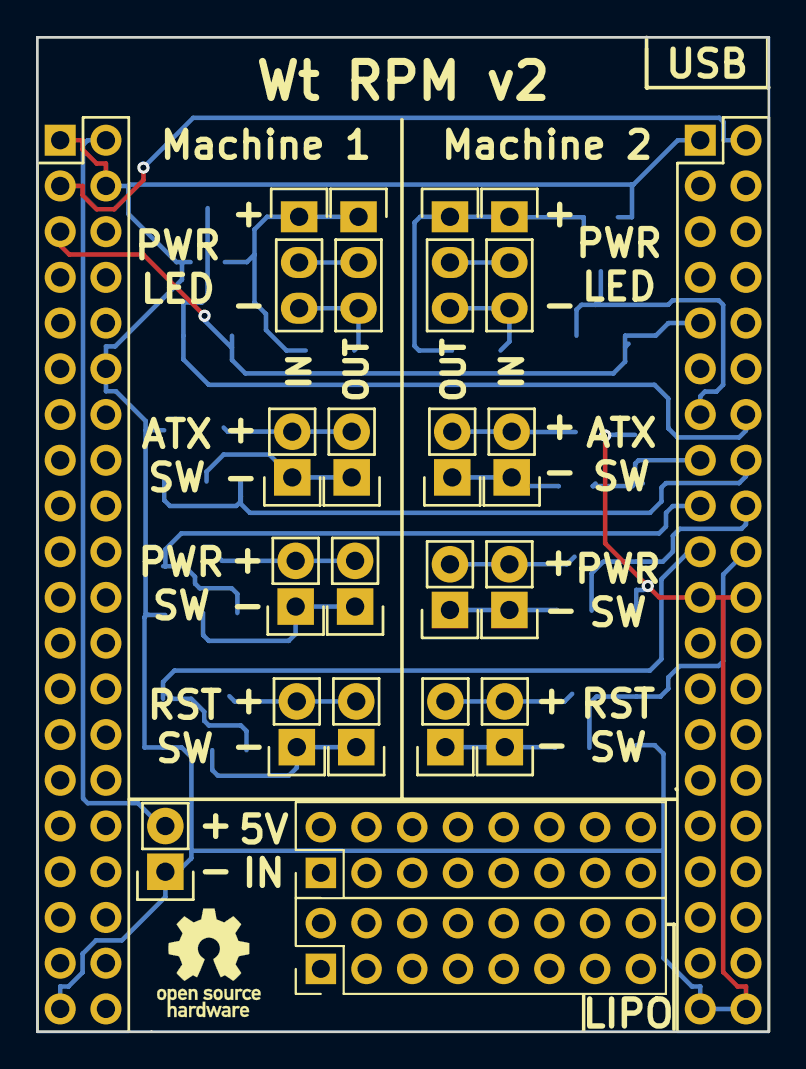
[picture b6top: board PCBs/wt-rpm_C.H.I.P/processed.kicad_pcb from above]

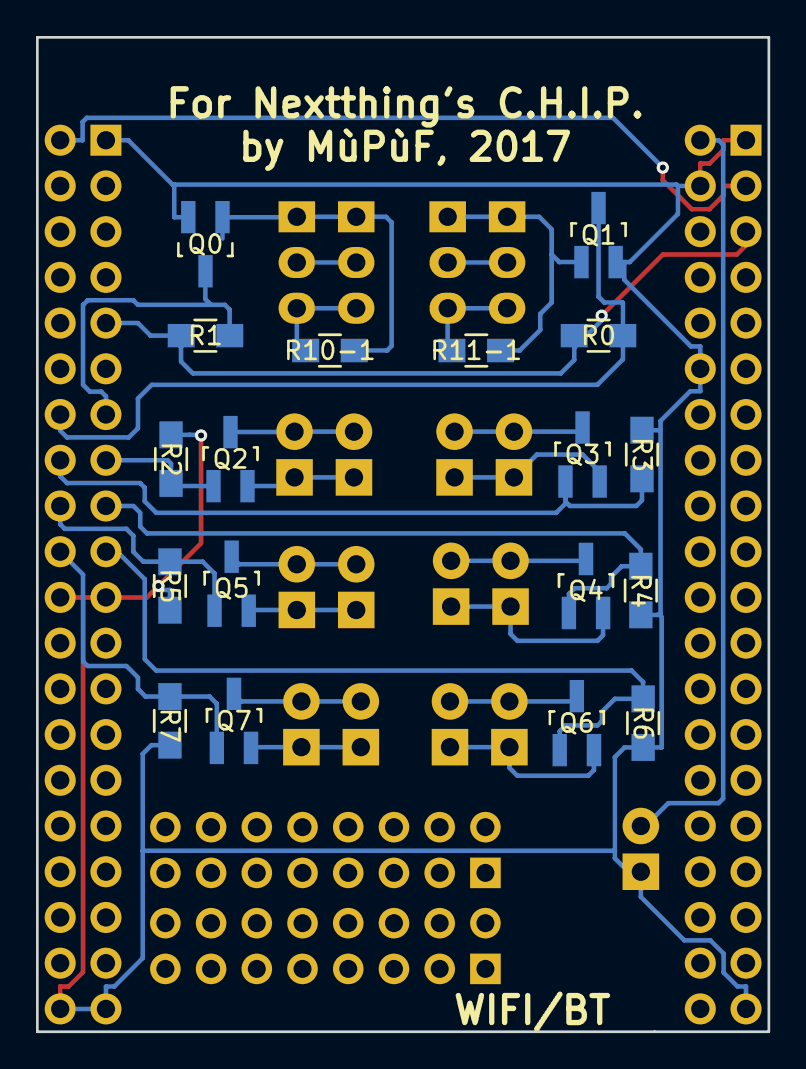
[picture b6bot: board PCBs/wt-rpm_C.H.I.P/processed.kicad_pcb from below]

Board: 2 copper layers, 40.6 x 55.2 mm, 39 parts (18 on the bottom side), 30 nets.

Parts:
J13, J14: DIP-HEADER-2x20; DIP_Header_2x20
P0, P0-1, P1-0, P1-1: CONN_01X03; Pin_Header_Straight_1x03
P2-0, P2-1, P3-0, P3-1, P4-0, P4-1, P5-0, P5-1, P6-0, P6-1, P7-0, P7-1, P7-CHG1: CONN_01X02; Pin_Header_Straight_1x02
Q0, Q1: SOT-23_Handsoldering
Q2, Q3, Q4, Q5, Q6, Q7: MOSFET-NCHANNELSMD; SOT-23_Handsoldering
R0, R1, R2, R3, R4, R5, R6, R7, R10-1, R11-1: 10k; R_0805_HandSoldering
SCRATCH0, SCRATCH1: Pin_Header_Straight_2x08_Pitch2.54mm

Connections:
+3.3V: J13.5, J14.9, R0.2, R1.1
+5V: J13.3, J14.2
/XIO-P0: J14.13, Q0.3, R1.2
/XIO-P1: J14.14, Q1.3, R0.1
/XIO-P2: J14.15, Q2.1, R2.1
/XIO-P3: J14.16, Q3.1, R3.1
/XIO-P4: J14.17, Q4.1, R4.1
/XIO-P5: J14.18, Q5.1, R5.1
/XIO-P6: J14.19, Q6.1, R6.1
/XIO-P7: J14.20, Q7.1, R7.1
GND: J13.1, J13.4, J13.12, J13.39, J14.1, J14.21, J14.22, J14.39, J14.40, P7-CHG1.1, Q0.2, Q1.2, R2.2, R3.2, R4.2, R5.2, R6.2, R7.2
unnamed: P0.1, P0-1.1, Q0.1, R10-1.2
unnamed: P0.2, P0-1.2
unnamed: P0.3, P0-1.3, R10-1.1
unnamed: P1-0.1, P1-1.1, Q1.1, R11-1.2
unnamed: P1-0.2, P1-1.2
unnamed: P1-0.3, P1-1.3, R11-1.1
unnamed: P2-0.1, P2-1.1, Q2.2
unnamed: P2-0.2, P2-1.2, Q2.3
unnamed: P3-0.1, P3-1.1, Q3.2
unnamed: P3-0.2, P3-1.2, Q3.3
unnamed: P4-0.1, P4-1.1, Q4.2
unnamed: P4-0.2, P4-1.2, Q4.3
unnamed: P5-0.1, P5-1.1, Q5.2
unnamed: P5-0.2, P5-1.2, Q5.3
unnamed: P6-0.1, P6-1.1, Q6.2
unnamed: P6-0.2, P6-1.2, Q6.3
unnamed: P7-0.1, P7-1.1, Q7.2
unnamed: P7-0.2, P7-1.2, Q7.3
VCHG: J13.2, P7-CHG1.2

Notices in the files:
PCBs/wt-rpm_C.H.I.P/processed.kicad_pcb:
Released under the CERN Open Hardware License v1.2
